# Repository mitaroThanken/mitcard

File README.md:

# mitcard

自作キーボードの習作。

## 特徴

* [Teency LC](https://www.pjrc.com/teensy/teensyLC.html)/[Teency 3.2](https://www.pjrc.com/teensy/teensy31.html)両対応
* 2x2のキーマトリックス
* [スイッチ用PCBソケット](https://yushakobo.jp/shop/a01ps/)使用
* 2つのタッチキー
* [modulo](http://biacco42.hatenablog.com/entry/2018/12/13/063814) 互換のジャック (※1)
* [SparkFun TeencyView](https://www.sparkfun.com/products/14048) 搭載可能 (※2)
* その他I/Oピンを外出し (※2)

※1 ソフトウェアは未対応、また、Teency LCは5Vトレラントではないことに注意。
※2 一部ピンが重複しています。

## 基板以外の材料

### 必須

* [Teency LC](https://www.pjrc.com/teensy/teensyLC.html)、または、[Teency 3.2](https://www.pjrc.com/teensy/teensy31.html)
  どちらかを用意してください。Modulo Pendant 互換を目指す場合は[Teency 3.2](https://www.pjrc.com/teensy/teensy31.html)一択です。
* ピンヘッダ・ピンソケット
  ボード内側のピンは使用していません。ですので、ボードの縁にあるスルーホールの数に対応したピンヘッダ・ピンソケットを用意してください。
  [スイッチサイエンス取扱のSparkFun製のもの](https://www.switch-science.com/catalog/2851/)とピンソケットでもよいです。

## メカニカルキーボードにするのに必須

以下のものをそれぞれ4つ用意してください。

* [スイッチ用PCBソケット](https://yushakobo.jp/shop/a01ps/)使用
* キースイッチ
  MX互換とKailh Chocに対応します。お好きなものをどうぞ。

## Modulo Pendant 互換品にするのに必須

以下のものをそれぞれ2つ用意してください。

* [MJ-4PP-9](http://akizukidenshi.com/catalog/g/gC-06070/)
* 抵抗
  (抵抗の大きさについては現在検討中。)

## OLED をつける場合

[SparkFun TeencyView](https://www.sparkfun.com/products/14048)が使用可能です。

ただし、D/Cを5ピンから21ピンに変更する必要があります。[ここ](https://learn.sparkfun.com/tutorials/teensyview-hookup-guide)を参考にデフォルトのラインを切って、21ピンの方にハンダでつなげてください。

(以降、更新予定)

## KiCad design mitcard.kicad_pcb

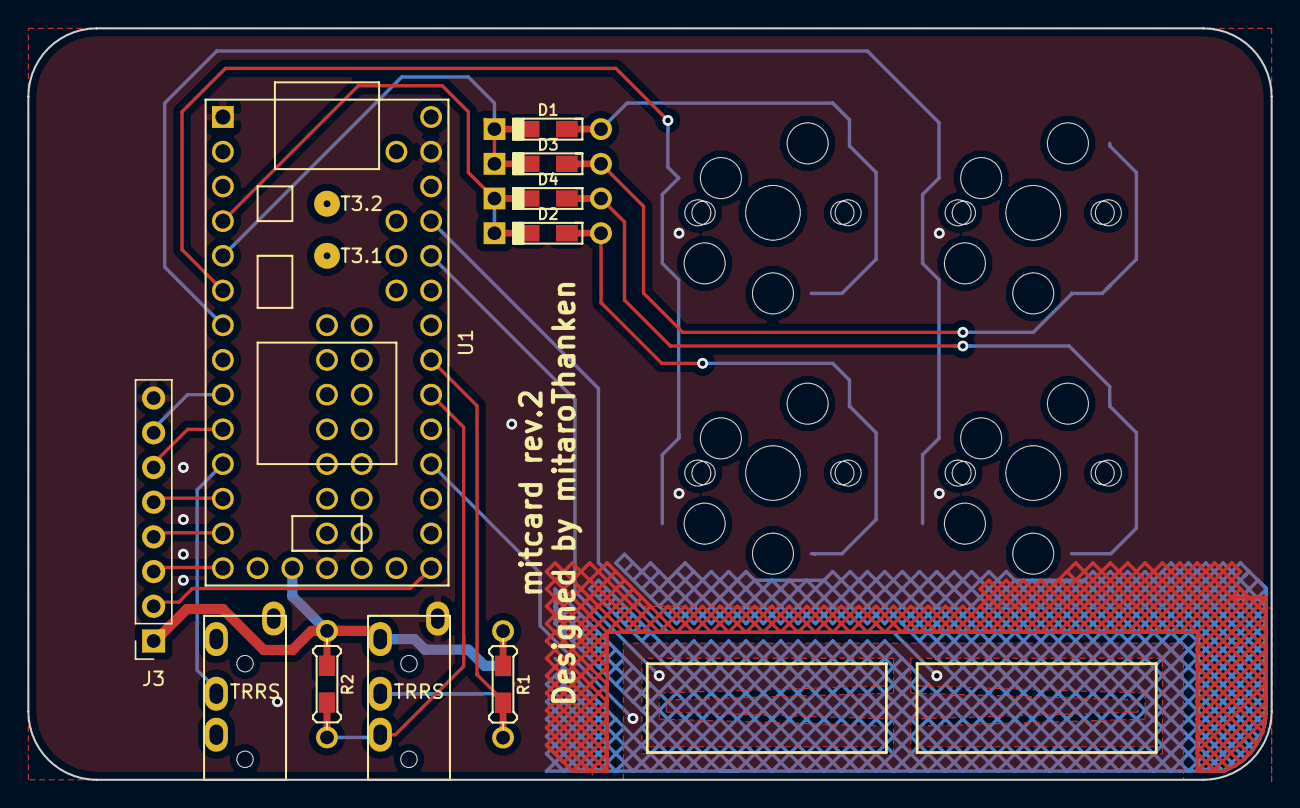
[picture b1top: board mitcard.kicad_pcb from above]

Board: 2 copper layers, 91.0 x 55.0 mm, 14 parts (0 on the bottom side), 19 nets.

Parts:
D1, D2, D3, D4: D; Diode-dual
J1, J2: MJ-4PP-9; MJ-4PP-9_1side
J3: Conn_01x08; PinSocket_1x08_P2.54mm_Vertical
R1, R2: 4.7K; Resistor-Hybrid
SW1, SW2, SW3, SW4: SW_PUSH; CherryMX_Choc_Hotswap_1side
U1: Teensy-LC; Teensy30_31_32_LC

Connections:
/3.3V: J1.D, J3.1, R1.1, R2.1, U1.16
/INT: J2.C, U1.11
/SCL: J1.C, R1.2, U1.26
/SDA: J1.B, R2.2, U1.25
/col1row0: D3.2, SW3.2
CS: J3.5, U1.12
GND: J1.A, J3.8, U1.1, U1.17, U1.32
MISO: J3.3, U1.14
MOSI: J3.4, U1.13
unnamed: D1.2, SW1.2
unnamed: D2.2, SW2.2
unnamed: D4.2, SW4.2
RX: J3.7, U1.9
SCK: J3.2, U1.20
TX: J3.6, U1.10
col0: SW1.1, SW2.1, U1.6
col1: SW3.1, SW4.1, U1.7
row0: D1.1, D3.1, U1.5
row1: D2.1, D4.1, U1.4

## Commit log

2019-03-17 Create project.
2019-03-17 [WIP] Add meta.
2019-03-17 Add lib dir.
2019-03-17 Add https://github.com/foostan/kbd
2019-03-17 Add https://github.com/keebio/Keebio-Parts.pretty
2019-03-17 Add https://github.com/XenGi/teensy*
    * https://github.com/XenGi/teensy_library
    * https://github.com/XenGi/teensy.pretty
2019-03-17 Add info of icon.
2019-03-18 テンプレートからの作成直後
2019-03-18 [wip] とりあえず配置
    キースイッチ、左側に持ってきたほうがいいかもしれない。
2019-03-21 タッチセンサー部を除いて仮配線完了？
2019-03-21 INT ピン変更
2019-03-21 SPI と I2C を引っ張り出しておく
2019-03-21 タッチパッド部も書いた
2019-03-25 ガーバーデータ出力
2019-03-30 出来上がった基板の写真を追加
2019-03-30 動作確認用スケッチ
    Teensyduino 使用。
2019-04-06 foostan/kbd をフォークしたリポジトリを参照するように変更
2019-04-06 キースイッチのソケット、片面のみのフットプリントが入っているブランチに切り替え
2019-04-06 足の置き場を確保
2019-04-07 gvr 出力
2019-05-04 スイッチのテストとタッチのテストを一本化
2019-05-16 TeencyView のテストコードを追加
    cf. https://learn.sparkfun.com/tutorials/teensyview-hookup-guide
2019-05-16 サンプルコードを統合
2019-05-17 Update README.md
    テンプレートのREADME.mdをmitcardのREADMEに書き換え開始。
2019-05-18 meishi展展示バージョン
